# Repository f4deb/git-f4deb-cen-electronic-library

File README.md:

cen-electronic-library
=====================

Library of all Schema of all electronical boards of Cybernetique en Nord

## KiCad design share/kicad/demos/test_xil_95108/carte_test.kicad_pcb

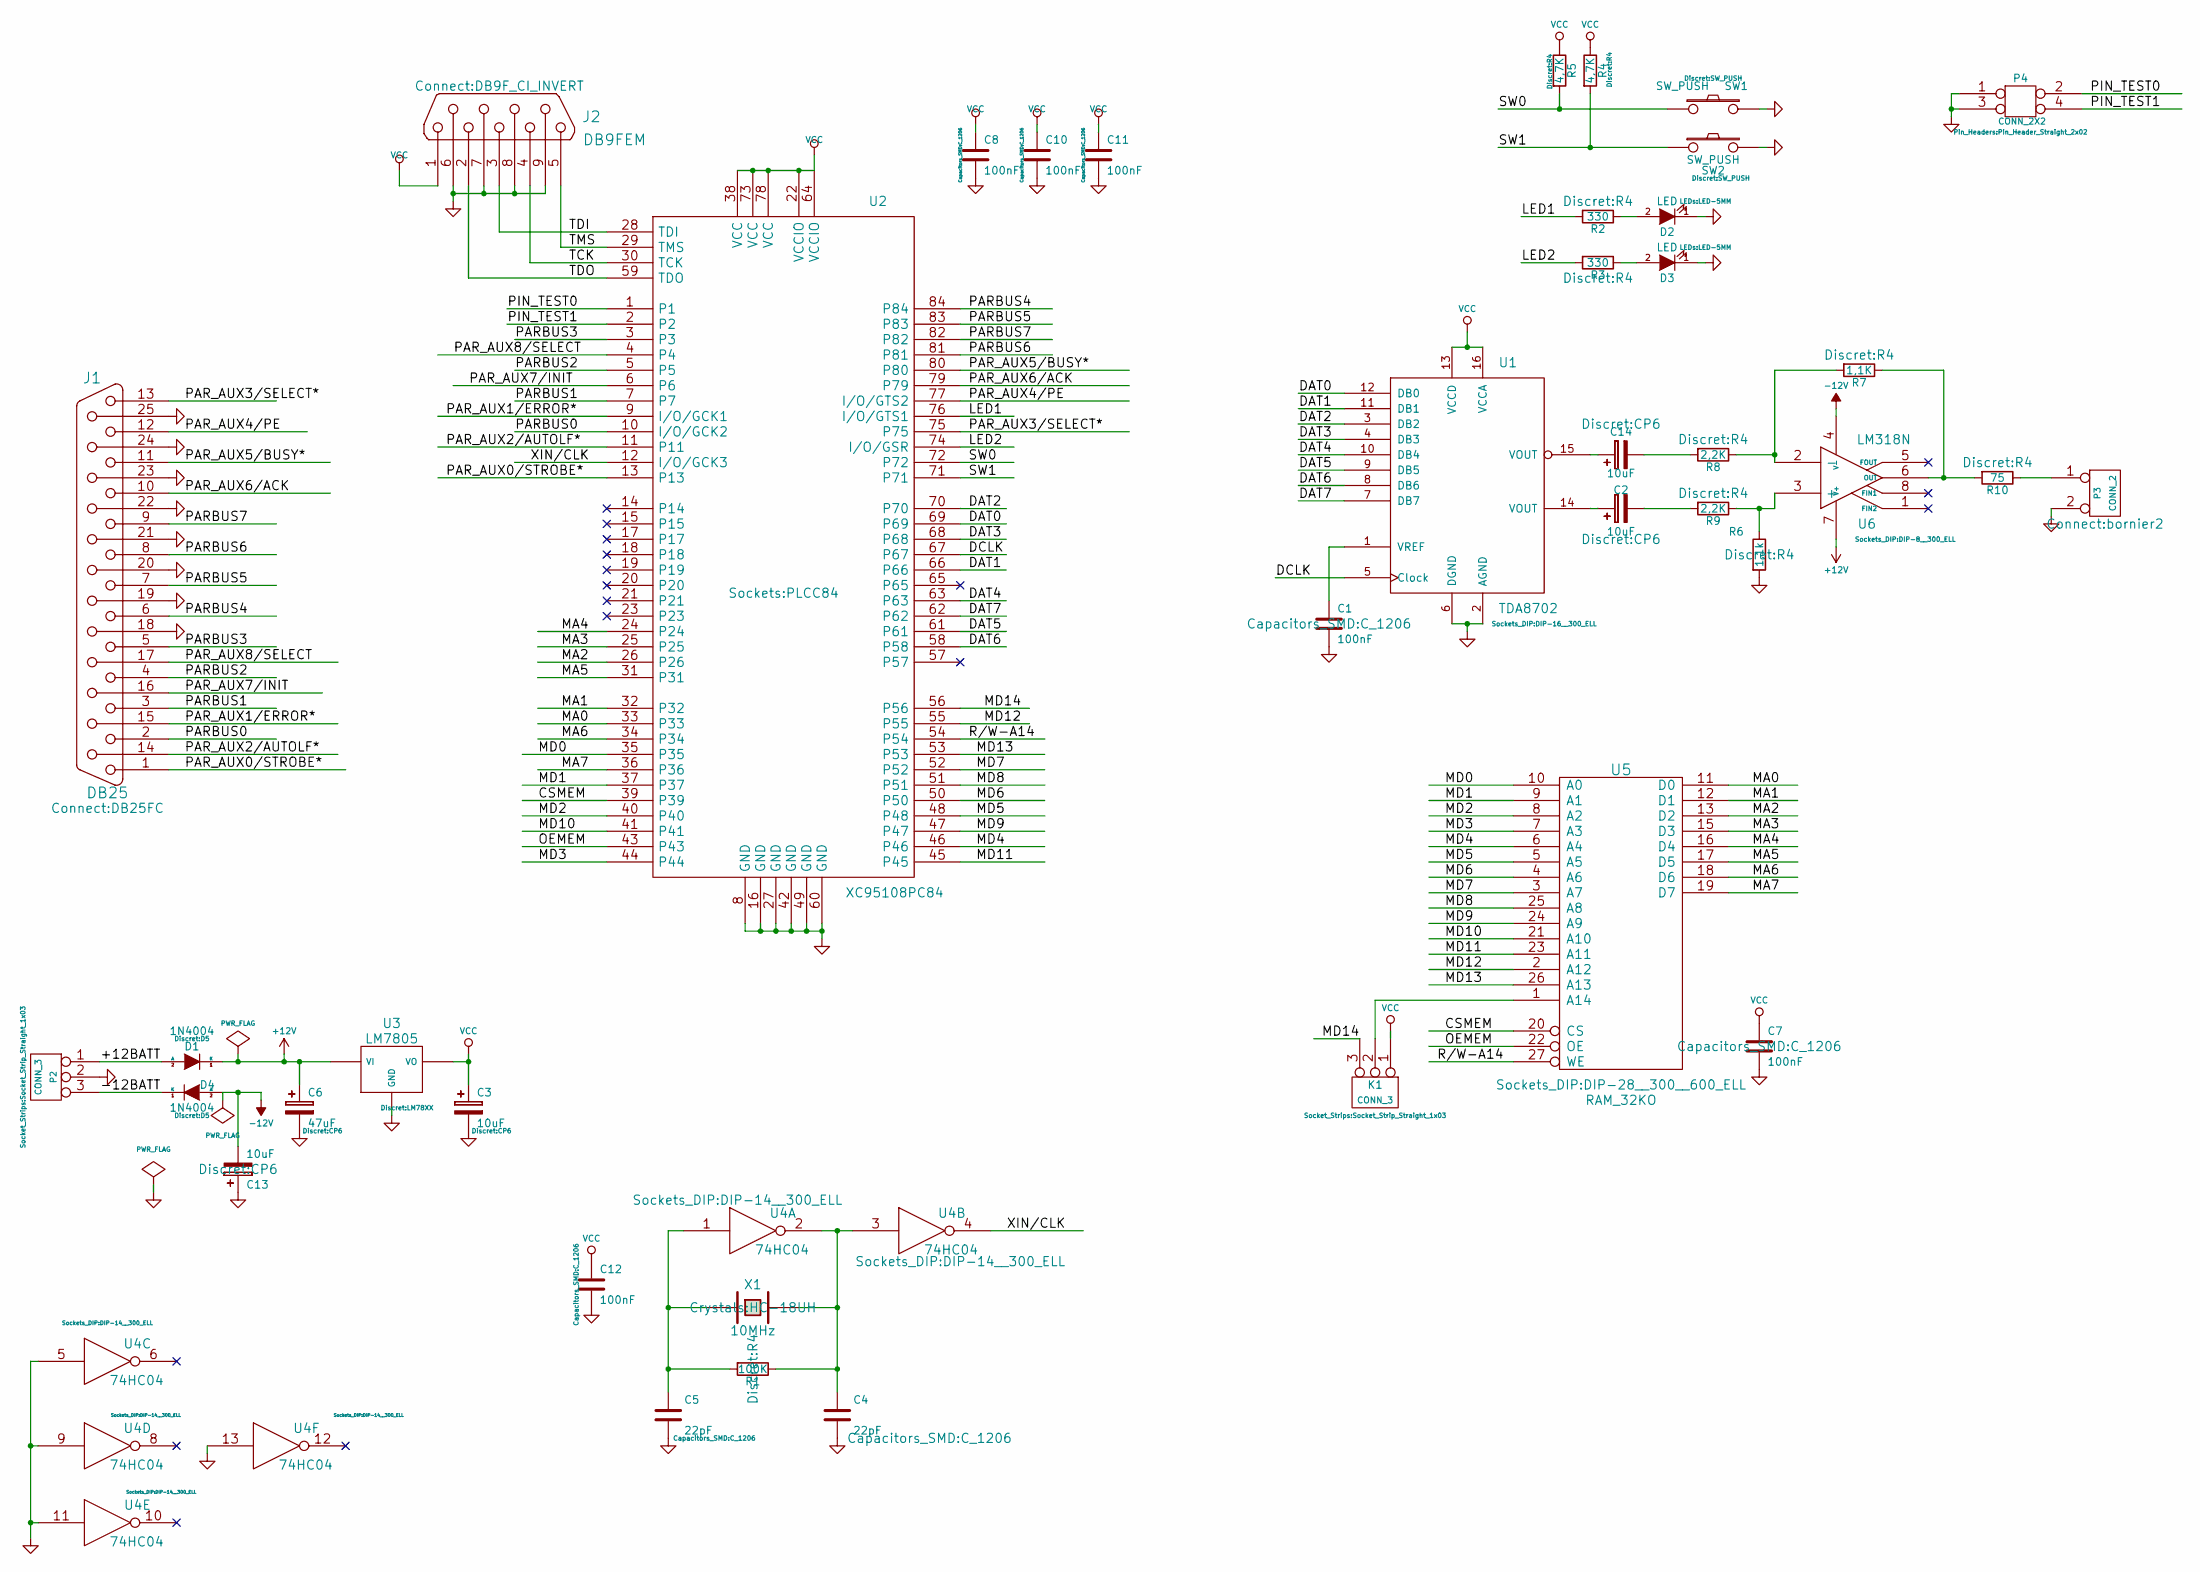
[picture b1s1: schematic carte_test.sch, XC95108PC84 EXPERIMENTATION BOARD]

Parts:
C1, C7, C8, C10, C11, C12: 100nF; C_1206
C2, C3, C13, C14: 10uF; CP6
C4, C5: 22pF; C_1206
C6: 47uF; CP6
D1, D4: 1N4004; D5
D2, D3: LED; LED-5MM
J1: DB25; DB25FC
J2: DB9FEM; DB9F_CI_INVERT
K1: CONN_3; Socket_Strip_Straight_1x03
P2: CONN_3; Socket_Strip_Straight_1x03
P3: CONN_2; bornier2
P4: CONN_2X2; Pin_Header_Straight_2x02
R1: 100K; R4
R2, R3: 330; R4
R4, R5: 4,7K; R4
R6: 1,1k; R4
R7: 1,1K; R4
R8, R9: 2,2K; R4
R10: 75; R4
SW1, SW2: SW_PUSH
U1: TDA8702; DIP-16__300_ELL
U2: XC95108PC84; PLCC84
U3: LM7805; LM78XX
U4: 74HC04; DIP-14__300_ELL
U5: RAM_32KO; DIP-28__300__600_ELL
U6: LM318N; DIP-8__300_ELL
X1: 10MHz; HC-18UH

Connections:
+12V: C6.1, D1.1 (K), U3.VI, U6.7 (V+)
-12V: C13.2, D4.2 (A), U6.4 (V-)
/+12BATT: D1.2 (A), P2.1
/-12BATT: D4.1 (K), P2.3
/CSMEM: U2.39, U5.20 (CS)
/DAT0: U1.12 (DB0), U2.69
/DAT1: U1.11 (DB1), U2.66
/DAT2: U1.3 (DB2), U2.70
/DAT3: U1.4 (DB3), U2.68
/DAT4: U1.10 (DB4), U2.63
/DAT5: U1.9 (DB5), U2.61
/DAT6: U1.8 (DB6), U2.58
/DAT7: U1.7 (DB7), U2.62
/DCLK: U1.5 (Clock), U2.67
/LED1: R2.2, U2.76 (I/O/GTS1)
/LED2: R3.2, U2.74 (I/O/GSR)
/MA0: U2.33, U5.11 (D0)
/MA1: U2.32, U5.12 (D1)
/MA2: U2.26, U5.13 (D2)
/MA3: U2.25, U5.15 (D3)
/MA4: U2.24, U5.16 (D4)
/MA5: U2.31, U5.17 (D5)
/MA6: U2.34, U5.18 (D6)
/MA7: U2.36, U5.19 (D7)
/MD0: U2.35, U5.10 (A0)
/MD1: U2.37, U5.9 (A1)
/MD2: U2.40, U5.8 (A2)
/MD3: U2.44, U5.7 (A3)
/MD4: U2.46, U5.6 (A4)
/MD5: U2.48, U5.5 (A5)
/MD6: U2.50, U5.4 (A6)
/MD7: U2.52, U5.3 (A7)
/MD8: U2.51, U5.25 (A8)
/MD9: U2.47, U5.24 (A9)
/MD10: U2.41, U5.21 (A10)
/MD11: U2.45, U5.23 (A11)
/MD12: U2.55, U5.2 (A12)
/MD13: U2.53, U5.26 (A13)
/MD14: K1.3, U2.56
/OEMEM: U2.43, U5.22 (OE)
/PARBUS0: J1.2, U2.10 (I/O/GCK2)
/PARBUS1: J1.3, U2.7
/PARBUS2: J1.4, U2.5
/PARBUS3: J1.5, U2.3
/PARBUS4: J1.6, U2.84
/PARBUS5: J1.7, U2.83
/PARBUS6: J1.8, U2.81
/PARBUS7: J1.9, U2.82
/PAR_AUX0/STROBE*: J1.1, U2.13
/PAR_AUX1/ERROR*: J1.15, U2.9 (I/O/GCK1)
/PAR_AUX2/AUTOLF*: J1.14, U2.11
/PAR_AUX3/SELECT*: J1.13, U2.75
/PAR_AUX4/PE: J1.12, U2.77 (I/O/GTS2)
/PAR_AUX5/BUSY*: J1.11, U2.80
/PAR_AUX6/ACK: J1.10, U2.79
/PAR_AUX7/INIT: J1.16, U2.6
/PAR_AUX8/SELECT: J1.17, U2.4
/PIN_TEST0: P4.2, U2.1
/PIN_TEST1: P4.4, U2.2
/R/W-A14: U2.54, U5.27 (WE)
/SW0: R5.2, SW1.1, U2.72
/SW1: R4.2, SW2.1, U2.71
/TCK: J2.4, U2.30 (TCK)
/TDI: J2.3, U2.28 (TDI)
/TDO: J2.2, U2.59 (TDO)
/TMS: J2.5, U2.29 (TMS)
/XIN/CLK: U2.12 (I/O/GCK3), U4.4
GND: C1.2, C3.2, C4.2, C5.2, C6.2, C7.2, C8.2, C10.2, C11.2, C12.2, C13.1, D2.1 (K), D3.1 (K), J1.18, J1.19, J1.20, J1.21, J1.22, J1.23, J1.24, J1.25, J2.6, J2.7, J2.8, J2.9, P2.2 (PM), P3.2 (PM), P4.1, P4.3, R6.2, SW1.2, SW2.2, U1.2 (AGND), U1.6 (DGND), U2.8 (GND), U2.16 (GND), U2.27 (GND), U2.42 (GND), U2.49 (GND), U2.60 (GND), U3.GND, U4.5, U4.7 (GND), U4.9, U4.11, U4.13, U5.14 (GND)
unnamed: C1.1, U1.1 (VREF)
unnamed: C2.1, U1.14 (VOUT)
unnamed: C2.2, R9.2
unnamed: C4.1, R1.1, U4.2, U4.3, X1.2
unnamed: C5.1, R1.2, U4.1, X1.1
unnamed: C14.1, U1.15 (VOUT)
unnamed: C14.2, R8.2
unnamed: D2.2 (A), R2.1
unnamed: D3.2 (A), R3.1
unnamed: K1.2 (PM), U5.1 (A14)
unnamed: P3.1, R10.1
unnamed: R6.1, R9.1, U6.3 (+)
unnamed: R7.2, R8.1, U6.2 (-)
unnamed: R7.1, R10.2, U6.6 (OUT)
VCC: C3.1, C7.1, C8.1, C10.1, C11.1, C12.1, J2.1, K1.1, R4.1, R5.1, U1.13 (VCCD), U1.16 (VCCA), U2.22 (VCCIO), U2.38 (VCC), U2.64 (VCCIO), U2.73 (VCC), U2.78 (VCC), U3.VO, U4.14 (VCC), U5.28 (VCC)

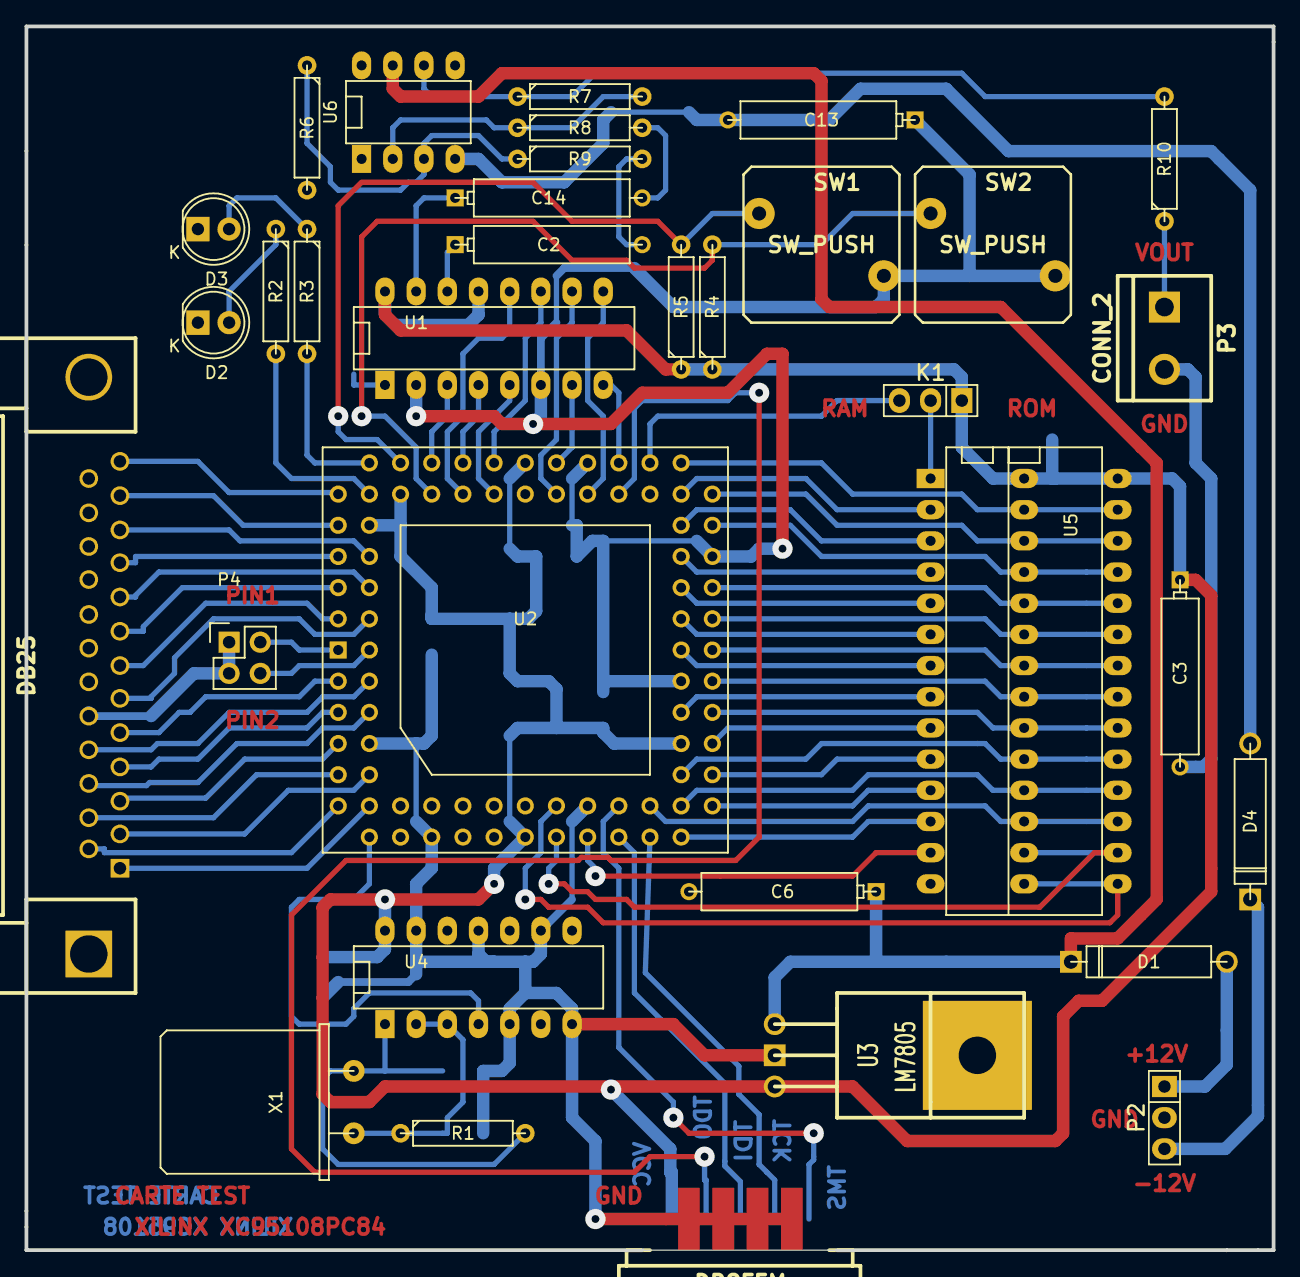
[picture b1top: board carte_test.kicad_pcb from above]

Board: 2 copper layers, 101.6 x 99.7 mm, 42 parts (0 on the bottom side), 83 nets.

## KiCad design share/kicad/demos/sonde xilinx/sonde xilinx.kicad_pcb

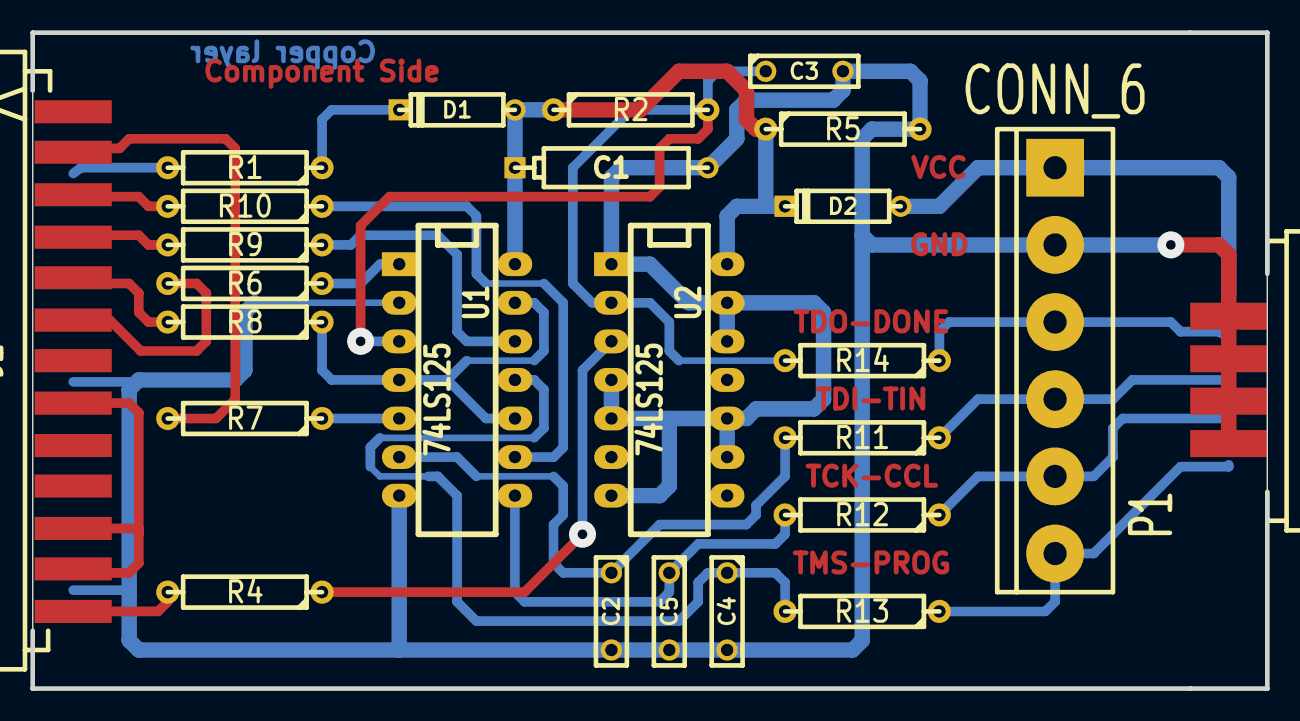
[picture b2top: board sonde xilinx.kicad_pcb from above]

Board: 2 copper layers, 81.3 x 43.2 mm, 25 parts (0 on the bottom side), 26 nets.

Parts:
C1: 1uF; CP5
C2, C3, C4, C5: 100pF; C2
D1, D2: BAT46; D3
J1: DB25MALE; DB25M_CI
J2: DB9MALE; DB9M_CI_INVERT
P1: CONN_6; bornier6
R1, R6, R7, R8, R9, R10, R11, R12, R13, R14: 100; R4
R2: 5,1K; R4
R4: 47; R4
R5: 1K; R4
U1, U2: 74LS125; 14DIP-ELL300

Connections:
/CLK-D1: J1.3, R10.2
/CTRL-D3: J1.5, R8.2
/DONE-SELECT*: J1.13, R4.2
/PWR_3,3-5V: D2.1, J2.1, P1.1
/TCK-CCLK: J2.4, P1.5, R12.1
/TD0-DONE: J2.2, P1.3, R14.1
/TD0-PROG-D4: J1.6, R6.2
/TDI-DIN: J2.3, P1.4, R11.1
/TDI-DIN-D0: J1.2, R7.2
/TMS-PROG: J2.5, P1.6, R13.1
/TMS-PROG-D2: J1.4, R9.2
/VCC_SENSE-ERROR*: J1.15, R1.2
GND: C1.2, C2.2, C3.2, C4.2, C5.2, J1.20, J1.25, J2.6, J2.7, J2.8, J2.9, P1.2, R5.2, U1.2, U1.7, U2.1, U2.4, U2.5, U2.7, U2.9, U2.10, U2.12, U2.13
unnamed: J1.8, J1.11, J1.12
unnamed: D1.2, R1.1
unnamed: R4.1, U2.3
unnamed: R7.1, U1.5
unnamed: R10.1, U1.9
unnamed: R6.1, U1.1
unnamed: R9.1, U1.12
unnamed: R8.1, U1.4, U1.10, U1.13
unnamed: C4.1, R13.2, U1.11
unnamed: C2.1, R11.2, U1.6
unnamed: C5.1, R12.2, U1.8
unnamed: C3.1, R2.2, R14.2, U1.3, U2.2
VCC: C1.1, D1.1, D2.2, R2.1, R5.1, U1.14, U2.14

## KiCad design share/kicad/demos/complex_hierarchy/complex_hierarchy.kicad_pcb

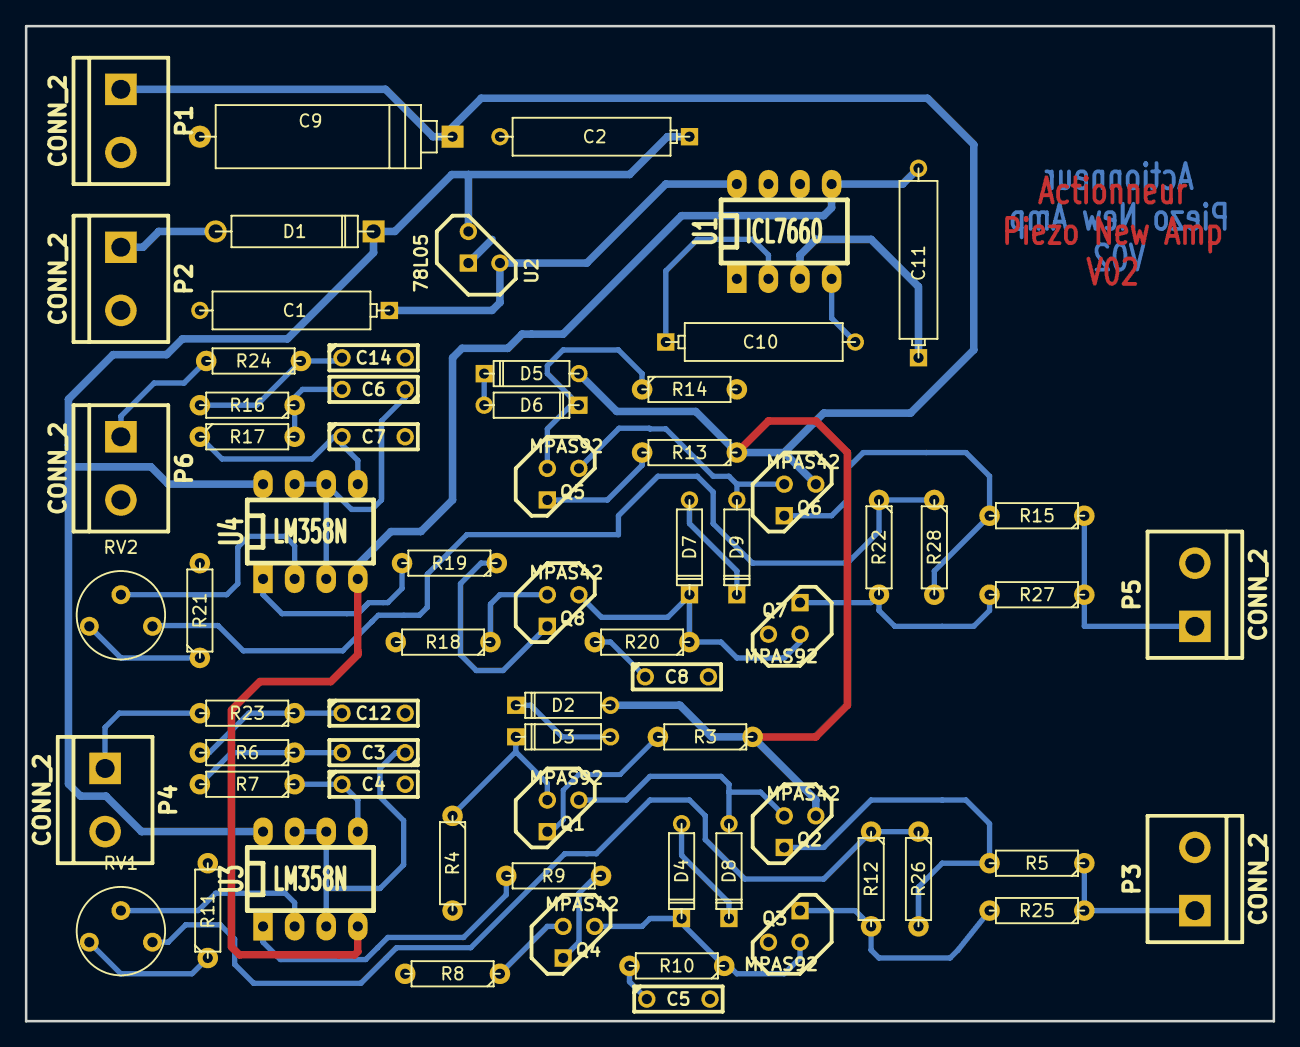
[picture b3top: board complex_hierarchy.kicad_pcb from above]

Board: 2 copper layers, 100.3 x 80.0 mm, 68 parts (0 on the bottom side), 50 nets.

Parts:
C1: 47uF; CP6
C2: 47uF/20V; CP6
C3, C6: 15nF; C2
C4, C7: 4.7nF; C2
C5, C8: 820pF; C2
C9: 47uF/63V; CP8
C10, C11: 10uF; CP6
C12, C14: 150nF; C2
D1: 1N4007; D5
D2, D3, D4, D5, D6, D7, D8, D9: 1N4148; D3
P1, P2, P3, P4, P5, P6: CONN_2; bornier2
Q1, Q3, Q5, Q7: MPAS92; TO92-CBE
Q2, Q4, Q6, Q8: MPAS42; TO92-CBE
R3, R13: 470; R3-LARGE_PADS
R4, R12, R14, R22, R26, R28: 220K; R3-LARGE_PADS
R5, R15, R25, R27: 47; R3-LARGE_PADS
R6, R7, R16, R17: 22K; R3-LARGE_PADS
R8, R9, R18, R19, R23, R24: 1K; R3-LARGE_PADS
R10, R20: 5,6K; R3-LARGE_PADS
R11, R21: 4,7K; R3-LARGE_PADS
RV1, RV2: 4,7K; RV2
U1: ICL7660; DIP-8__300_ELL
U2: 78L05; LM78LXX
U3, U4: LM358N; DIP-8__300_ELL

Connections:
+12V: C2.1, D1.1, U2.VI, U3.8, U4.8
-VAA: C11.2, U1.5, U3.4, U4.4
/12Vext: D1.2, P2.1
/ampli_ht_horizontal/PIEZO_IN: P6.1, R24.2
/ampli_ht_horizontal/PIEZO_OUT: P5.1, R15.1, R27.1
/ampli_ht_horizontal/S_OUT+: R22.1, R28.1, RV2.3
/ampli_ht_horizontal/Vpil_0_3,3V: C6.1, U4.3, U4.6, U4.7
/ampli_ht_vertical/PIEZO_IN: P4.1, R23.2
/ampli_ht_vertical/PIEZO_OUT: P3.1, R5.1, R25.1
/ampli_ht_vertical/S_OUT+: R12.1, R26.1, RV1.3
/ampli_ht_vertical/Vpil_0_3,3V: C3.1, U3.3, U3.6, U3.7
GND: C1.2, C2.2, C4.2, C5.2, C7.2, C8.2, C9.2, C11.1, C12.2, C14.2, P1.2, P2.2, P3.2, P4.2, P5.2, P6.2, Q3.C, Q7.C, R4.2, R8.2, R11.2, R14.2, R18.2, R21.2, U1.3, U2.GND
HT: C9.1, D2.2, D5.2, P1.1, Q2.C, Q6.C, R3.1, R13.1
unnamed: C3.2, R6.1, R7.2
unnamed: C4.1, R7.1, U3.5
unnamed: C5.1, R10.2
unnamed: C6.2, R16.1, R17.2
unnamed: C7.1, R17.1, U4.5
unnamed: C8.1, R20.2
unnamed: C10.1, U1.2
unnamed: C10.2, U1.4
unnamed: C12.1, R6.2, R23.1
unnamed: C14.1, R16.2, R24.1
unnamed: D2.1, D3.2
unnamed: D3.1, Q1.B, R4.1
unnamed: D4.1, Q3.B, Q4.C, R10.1
unnamed: D4.2, D8.1
unnamed: D5.1, D6.2
unnamed: D6.1, Q5.B, R14.1
unnamed: D7.1, Q7.B, Q8.C, R20.1
unnamed: D7.2, D9.1
unnamed: D8.2, Q1.C, Q2.B
unnamed: D9.2, Q5.C, Q6.B
unnamed: Q1.E, R3.2
unnamed: Q2.E, R5.2, R26.2
unnamed: Q3.E, R12.2, R25.2
unnamed: Q4.B, R8.1
unnamed: Q4.E, R9.1
unnamed: Q5.E, R13.2
unnamed: Q6.E, R15.2, R28.2
unnamed: Q7.E, R22.2, R27.2
unnamed: Q8.B, R18.1
unnamed: Q8.E, R19.1
unnamed: R9.2, U3.1
unnamed: R11.1, RV1.1
unnamed: R19.2, U4.1
unnamed: R21.1, RV2.1
unnamed: RV1.2, U3.2
unnamed: RV2.2, U4.2
VCC: C1.1, U1.8, U2.VO

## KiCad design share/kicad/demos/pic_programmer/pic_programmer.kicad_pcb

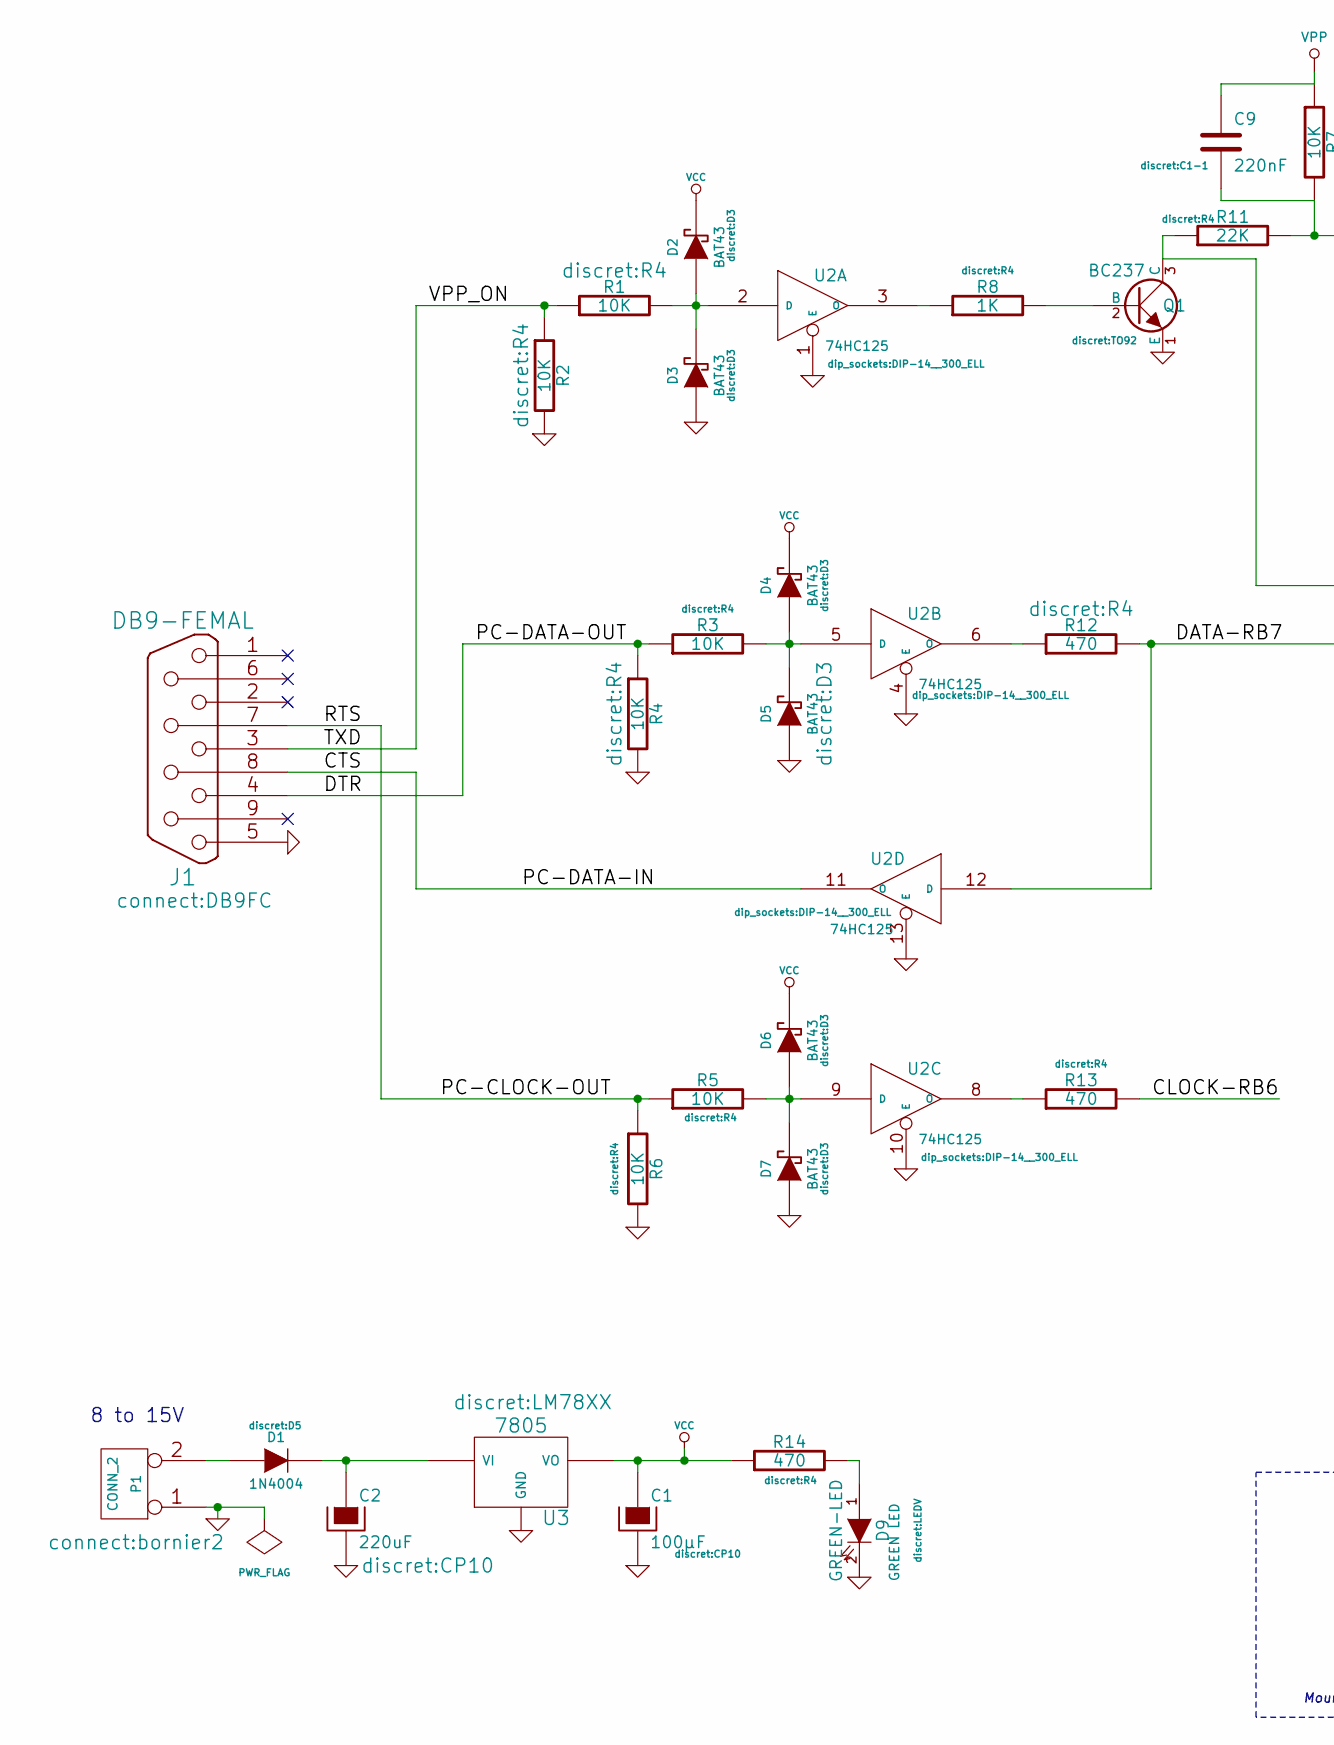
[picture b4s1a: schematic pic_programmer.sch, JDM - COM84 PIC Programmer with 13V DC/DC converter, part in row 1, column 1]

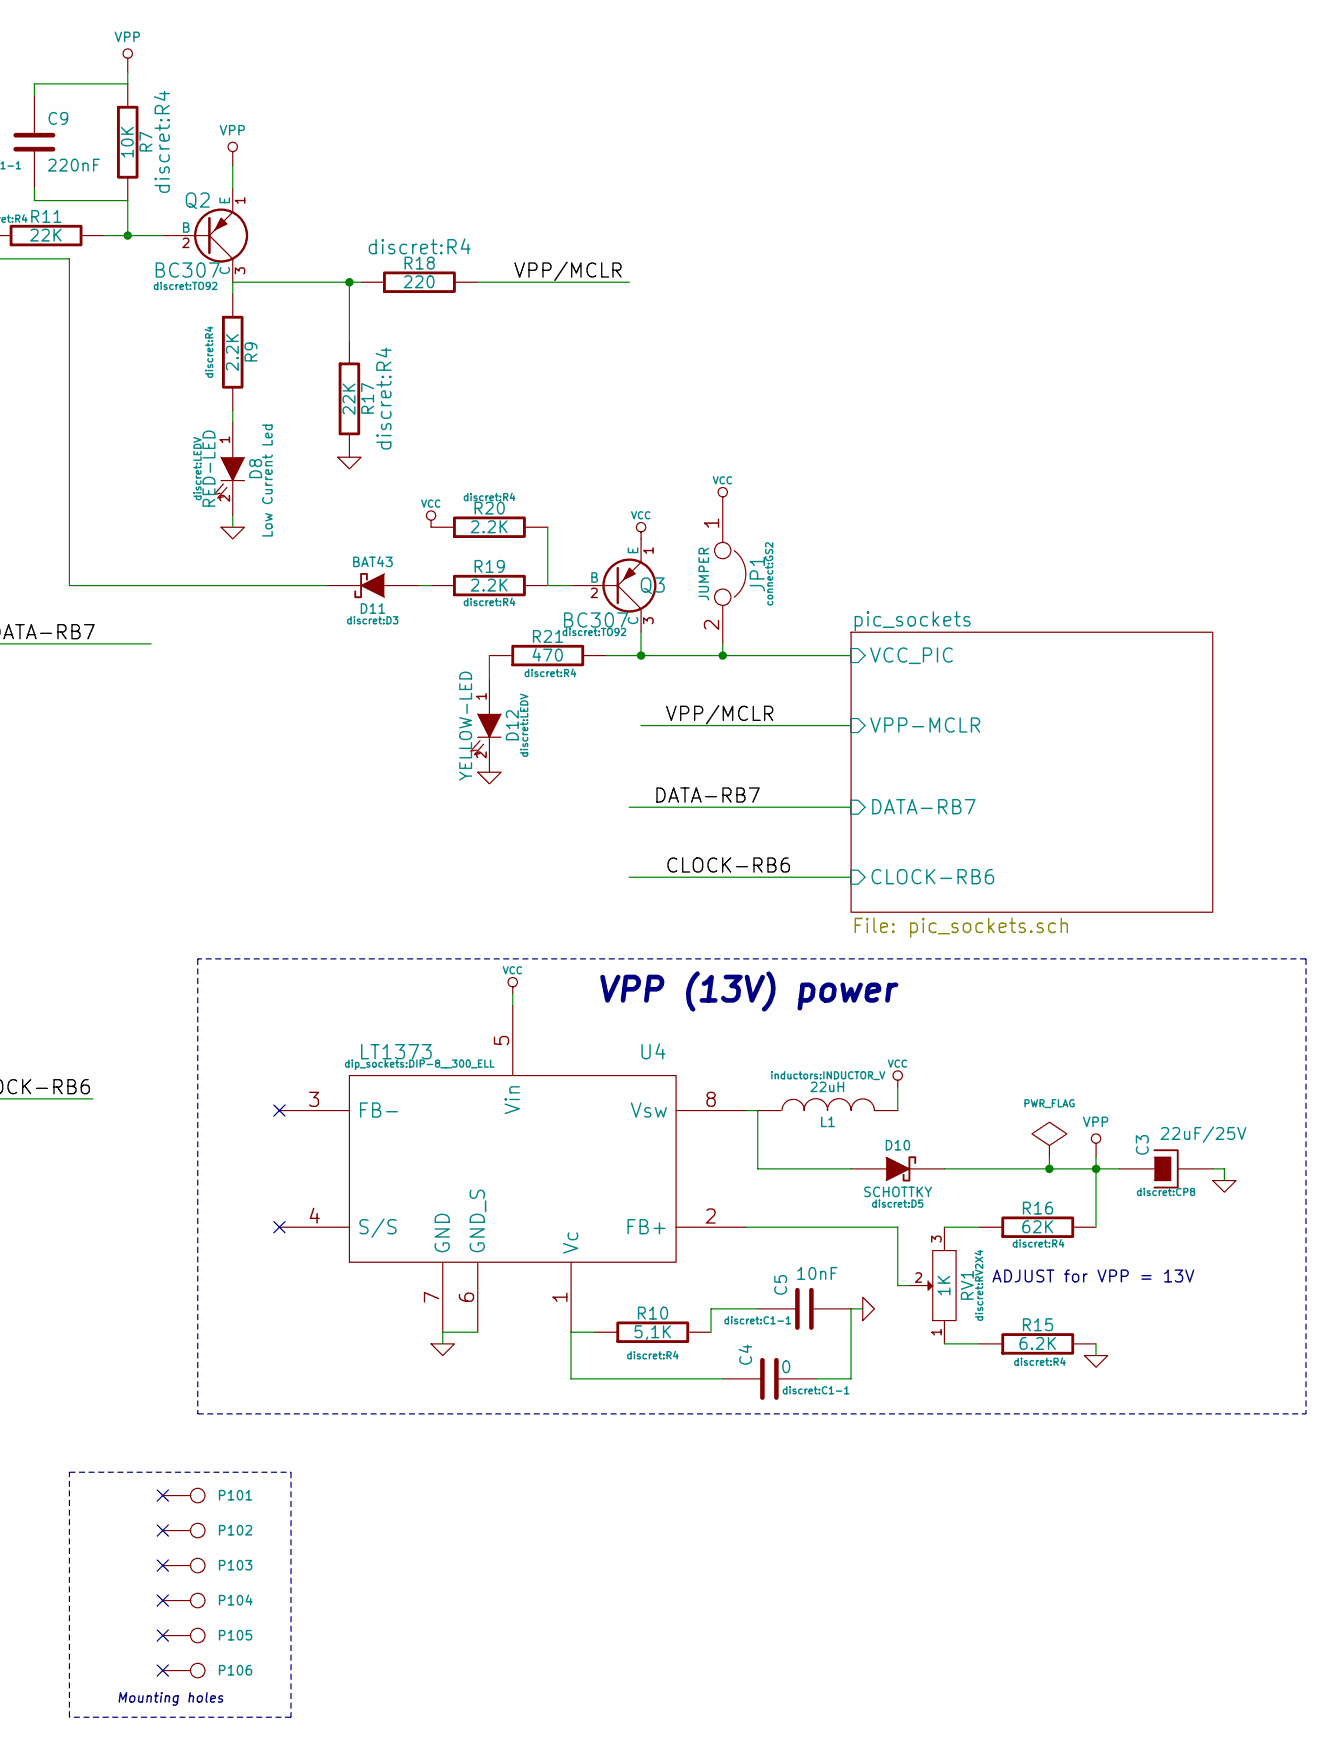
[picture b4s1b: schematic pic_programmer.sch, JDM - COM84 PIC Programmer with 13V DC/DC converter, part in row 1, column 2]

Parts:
C1: 100µF; CP10
C2: 220uF; CP10
C3: 22uF/25V; CP8
C4: 0; C1-1
C5: 10nF; C1-1
C9: 220nF; C1-1
D1: 1N4004; D5
D2, D3, D4, D5, D6, D7, D11: BAT43; D3
D8: RED-LED; LEDV
D9: GREEN-LED; LEDV
D10: SCHOTTKY; D5
D12: YELLOW-LED; LEDV
J1: DB9-FEMAL; DB9FC
JP1: JUMPER; GS2
L1: 22uH; INDUCTOR_V
P1: CONN_2; bornier2
P101, P102, P103, P104, P105, P106: CONN_1; 1pin-4
Q1: BC237; TO92
Q2, Q3: BC307; TO92
R1, R2, R3, R4, R5, R6, R7: 10K; R4
R8: 1K; R4
R9, R19, R20: 2.2K; R4
R10: 5,1K; R4
R11, R17: 22K; R4
R12, R13, R14, R21: 470; R4
R15: 6.2K; R4
R16: 62K; R4
R18: 220; R4
RV1: 1K; RV2X4
U2: 74HC125; DIP-14__300_ELL
U3: 7805; LM78XX
U4: LT1373; DIP-8__300_ELL

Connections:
/CTS: J1.8, U2.11 (O)
/DTR: J1.4, R3.1, R4.1
/PC-CLOCK-OUT: J1.7, R5.1, R6.1
/TXD: J1.3, R1.1, R2.1
/pic_sockets/CLOCK-RB6: R13.2; also elsewhere on the board
/pic_sockets/DATA-RB7: R12.2, U2.12 (D); also elsewhere on the board
/pic_sockets/VCC_PIC: JP1.2, Q3.3 (C), R21.2; also elsewhere on the board
/pic_sockets/VPP-MCLR: R18.2; also elsewhere on the board
GND: C1.2, C2.2, C3.2, C4.2, C5.2, D3.1 (A), D5.1 (A), D7.1 (A), D8.2 (K), D9.2 (K), D12.2 (K), J1.5, P1.1, Q1.1 (E), R2.2, R4.2, R6.2, R15.2, R17.2, U2.1 (E), U2.4 (E), U2.7 (GND), U2.10 (E), U2.13 (E), U3.GND, U4.6 (GND_S), U4.7 (GND); also elsewhere on the board
unnamed: C2.1, D1.2 (K), U3.VI
unnamed: C4.1, R10.1, U4.1 (Vc)
unnamed: C5.1, R10.2
unnamed: C9.2, Q2.2 (B), R7.2, R11.2
unnamed: D1.1 (A), P1.2 (PM)
unnamed: D2.1 (A), D3.2 (K), R1.2, U2.2 (D)
unnamed: D4.1 (A), D5.2 (K), R3.2, U2.5 (D)
unnamed: D6.1 (A), D7.2 (K), R5.2, U2.9 (D)
unnamed: D8.1 (A), R9.2
unnamed: D9.1 (A), R14.2
unnamed: D10.1 (A), L1.1, U4.8 (Vsw)
unnamed: D11.1 (A), R19.1
unnamed: D11.2 (K), Q1.3 (C), R11.1
unnamed: D12.1 (A), R21.1
unnamed: Q1.2 (B), R8.2
unnamed: Q2.3 (C), R9.1, R17.1, R18.1
unnamed: Q3.2 (B), R19.2, R20.2
unnamed: R8.1, U2.3 (O)
unnamed: R12.1, U2.6 (O)
unnamed: R13.1, U2.8 (O)
unnamed: R15.1, RV1.1
unnamed: R16.1, RV1.3
unnamed: RV1.2, U4.2 (FB+)
VCC: C1.1, D2.2 (K), D4.2 (K), D6.2 (K), JP1.1, L1.2, Q3.1 (E), R14.1, R20.1, U2.14 (VCC), U3.VO, U4.5 (Vin)
VPP: C3.1, C9.1, D10.2 (K), Q2.1 (E), R7.1, R16.2

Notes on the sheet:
ADJUST for VPP = 13V
8 to 15V
VPP (13V) power
Mounting holes

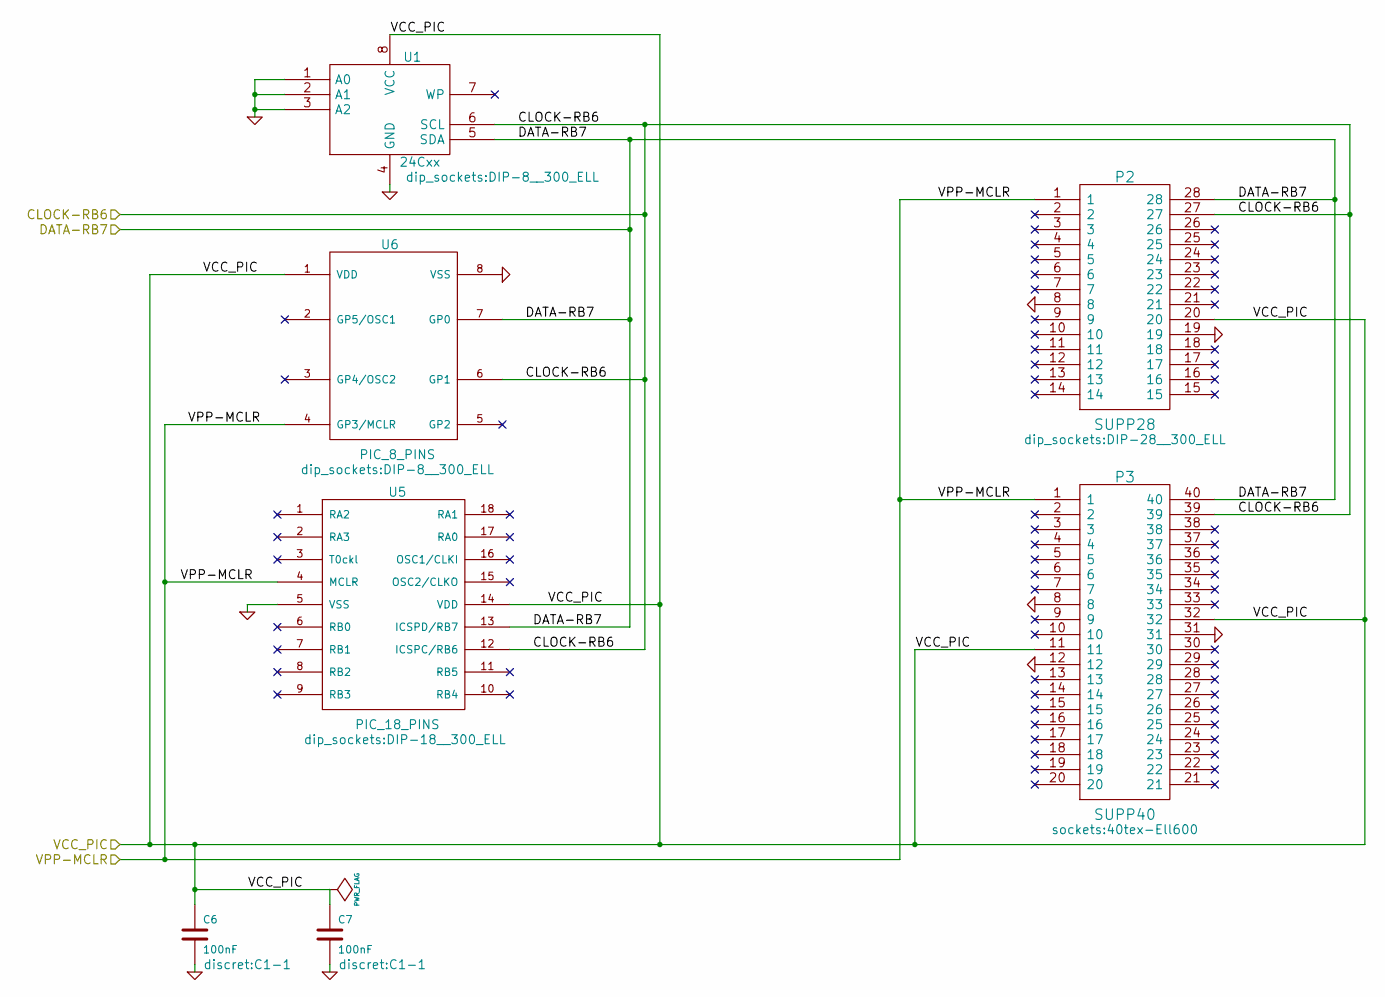
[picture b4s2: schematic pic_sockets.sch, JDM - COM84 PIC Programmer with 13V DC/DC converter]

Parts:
C6, C7: 100nF; C1-1
P2: SUPP28; DIP-28__300_ELL
P3: SUPP40; 40tex-Ell600
U1: 24Cxx; DIP-8__300_ELL
U5: PIC_18_PINS; DIP-18__300_ELL
U6: PIC_8_PINS; DIP-8__300_ELL

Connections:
/pic_sockets/CLOCK-RB6: P2.27, P3.39, U1.6 (SCL), U5.12 (ICSPC/RB6), U6.6 (GP1); also elsewhere on the board
/pic_sockets/DATA-RB7: P2.28, P3.40, U1.5 (SDA), U5.13 (ICSPD/RB7), U6.7 (GP0); also elsewhere on the board
/pic_sockets/VCC_PIC: C6.1, C7.1, P2.20, P3.11, P3.32, U1.8 (VCC), U5.14 (VDD), U6.1 (VDD); also elsewhere on the board
/pic_sockets/VPP-MCLR: P2.1, P3.1, U5.4 (MCLR), U6.4 (GP3/MCLR); also elsewhere on the board
GND: C6.2, C7.2, P2.8, P2.19, P3.8, P3.12, P3.31, U1.1 (A0), U1.2 (A1), U1.3 (A2), U1.4 (GND), U5.5 (VSS), U6.8 (VSS); also elsewhere on the board

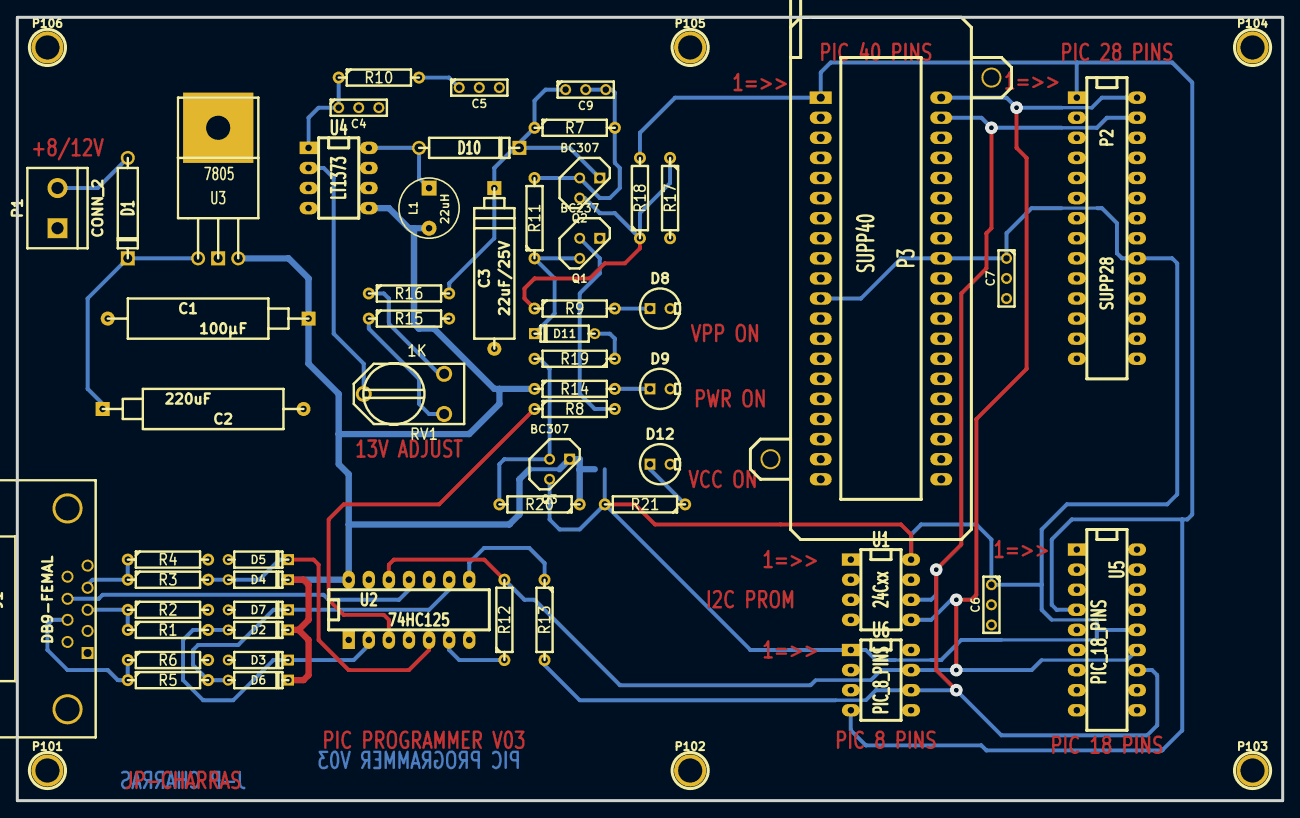
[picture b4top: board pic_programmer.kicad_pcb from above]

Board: 2 copper layers, 160.0 x 99.1 mm, 63 parts (1 on the bottom side), 34 nets.
